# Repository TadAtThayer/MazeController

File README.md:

# MazeController
Arduino Shield for ES28 project

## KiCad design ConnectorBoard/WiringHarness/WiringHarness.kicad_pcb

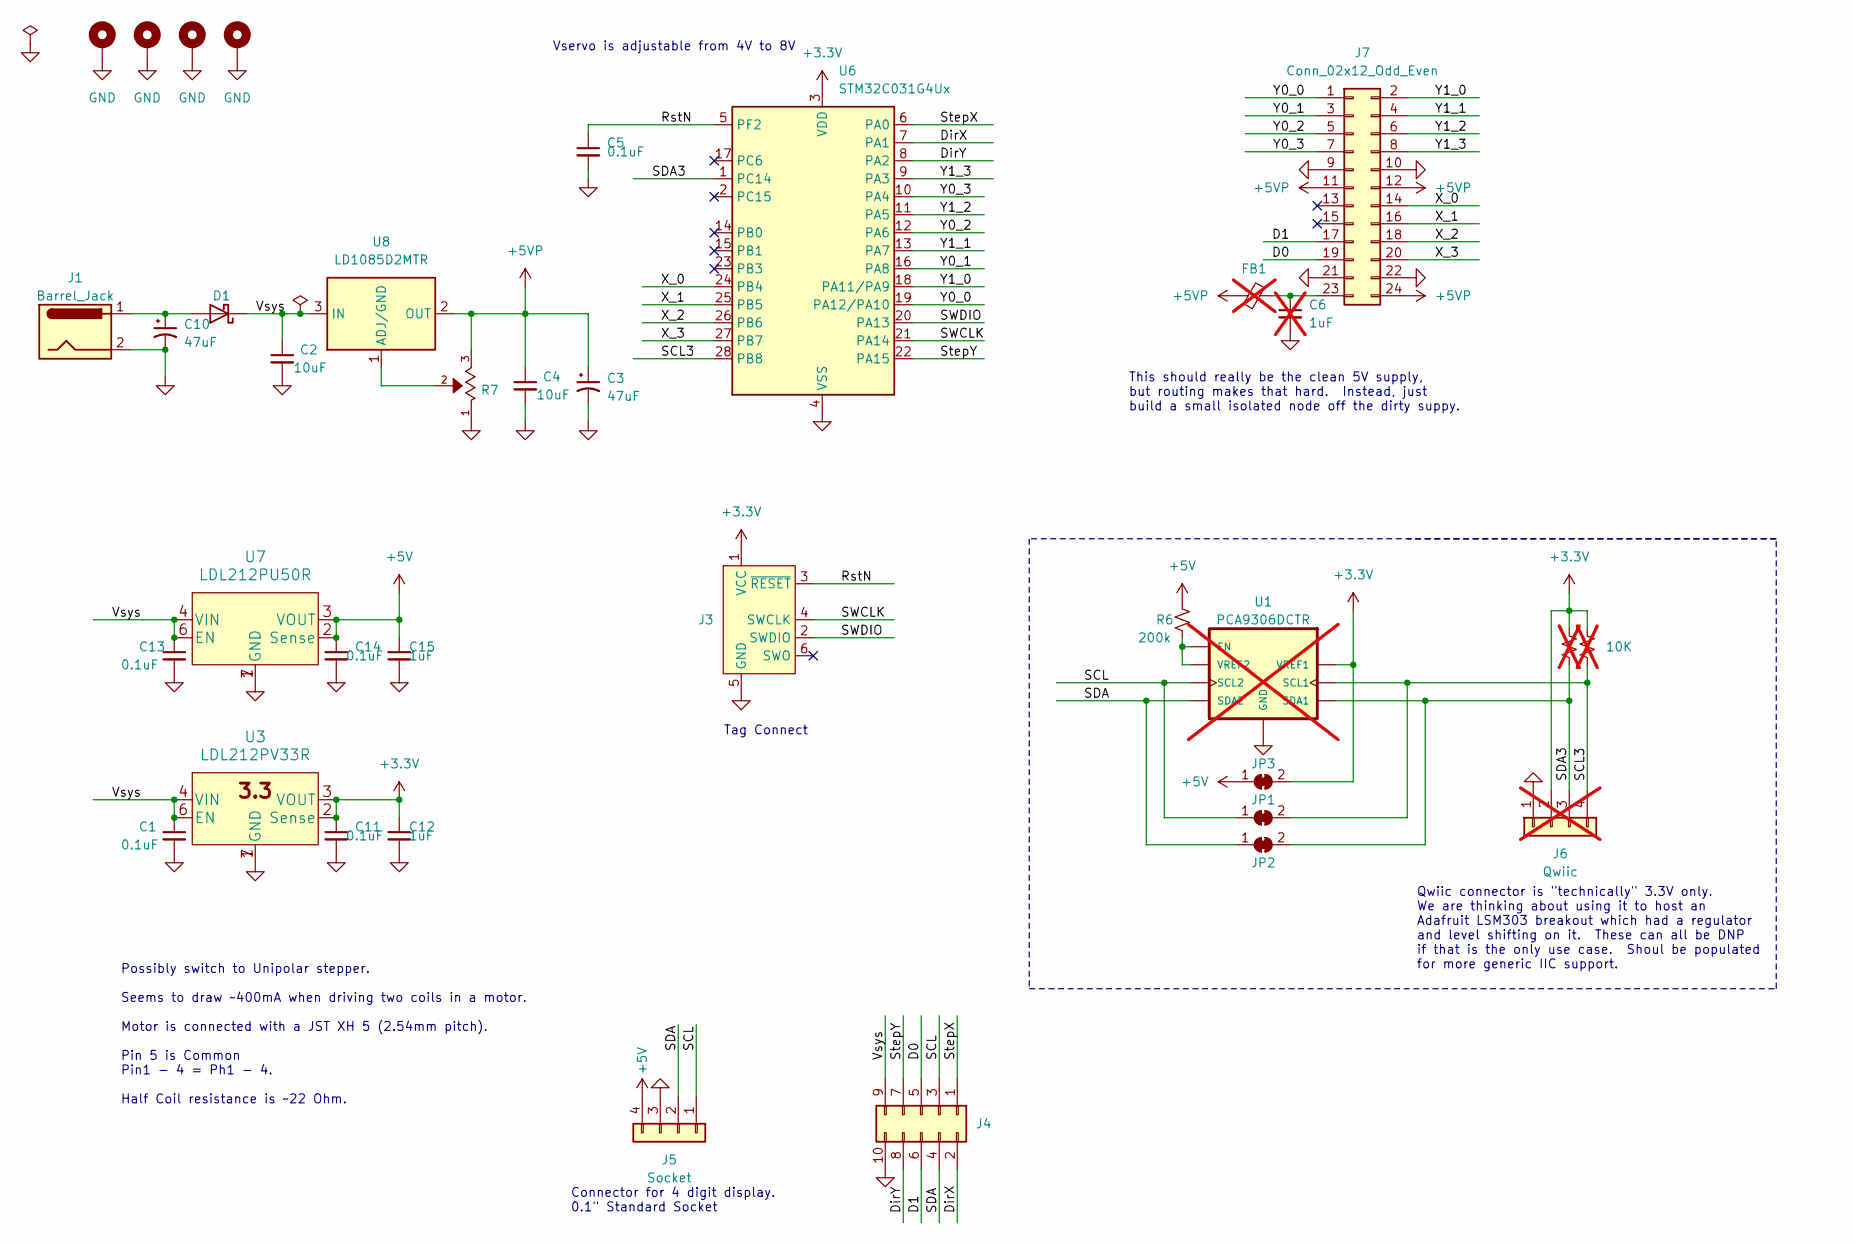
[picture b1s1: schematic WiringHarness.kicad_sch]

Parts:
C1, C5, C11, C13, C14: 0.1uF; C_0603_1608Metric; Digikey 1276-1861-1-ND
C2, C4: 10uF; C_0805_2012Metric; Digikey 490-10500-1-ND
C3, C10: 47uF; CP_Radial_D6.3mm_P2.50mm; Digikey 10-ECE-A1EKA470ICT-ND
C6: C_1U; C_0603_1608Metric; MPN CL10B105KA8NFNC; DigiKey PN 1276-1942-1-ND; not fitted
C12, C15: 1uF; C_0603_1608Metric; Digikey 1276-1861-1-ND
D1: D_Schottky; D_SMA; Digikey SK36A-LTPMSCT-ND
FB1: FB_120_100MHz; L_0603_1608Metric; DigiKey PN 490-16660-1-ND; not fitted
H1, H2, H3, H5: MountingHole_Pad; MountingHole_2.2mm_M2_Pad
J1: Barrel_Jack; BarrelJack_Horizontal; Digikey CP-002A-ND
J3: Conn_ARM_SWD_TagConnect_TC2030-NL; Tag-Connect_TC2030-IDC-NL_2x03_P1.27mm_Vertical
J4: Conn_02x05_Odd_Even; PinHeader_2x05_P2.54mm_Vertical; Digikey 732-2094-ND
J5: Socket; PinSocket_1x04_P2.54mm_Vertical; Digikey S7037-ND
J6: Qwiic; JST_SH_SM04B-SRSS-TB_1x04-1MP_P1.00mm_Horizontal; Digikey SM04B-SRSS-TB; not fitted
J7: Conn_02x12_Odd_Even; PinHeader_2x12_P2.54mm_Horizontal; Digikey 2057-PH2RA-24-UA-ND
JP1, JP2, JP3: SolderJumper_2_Bridged; SolderJumper-2_P1.3mm_Bridged_RoundedPad1.0x1.5mm
R1, R2: 10K; R_0603_1608Metric; Digikey RMCF0603FT10K0CT-ND; not fitted
R6: 200k; R_0603_1608Metric; Digikey RMCF0603FT200KCT-ND
R7: TC33X-2-102E; TRIM_TC33X-2-201E; Digikey TC33X-103ECT-ND
U1: PCA9306DCTR; MSOP-8_3x3mm_P0.65mm; Digikey 296-18509-1-ND; not fitted
U3: LDL212PV33R; LDL212_2x2mm_Pitch0.5mm; Digikey 497-19548-1-ND
U6: STM32C031G4Ux; QFN-28_4x4mm_P0.5mm; Digikey 497-STM32C031G6U6-ND
U7: LDL212PU50R; LDL212_3x3mm_Pitch0.95mm; Digikey 497-16897-1-ND
U8: LD1085D2MTR; TO-263-3_TabPin2; Digikey 497-3419-1-ND

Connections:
+3.3V: C11.1, C12.1, J3.1 (VCC), J6.2, JP3.2 (B), R1.1, R2.1, U1.2 (VREF1), U3.2 (Sense), U3.3 (VOUT), U6.3 (VDD)
+5V: C14.1, C15.1, J5.4, JP3.1 (A), R6.1, U7.2 (Sense), U7.3 (VOUT)
+5VP: C3.1, C4.1, FB1.1, J7.11, J7.12, J7.24, R7.3, U8.2 (OUT)
/D0: J4.5, J7.19
/D1: J4.6, J7.17
/DirX: J4.2, U6.7 (PA1)
/DirY: J4.8, U6.8 (PA2)
/RstN: C5.1, J3.3 (~RESET), U6.5 (PF2)
/SCL: J4.3, J5.1, JP1.1 (A), U1.6 (SCL2)
/SCL3: J6.4, JP1.2 (B), R1.2, U1.3 (SCL1), U6.28 (PB8)
/SDA: J4.4, J5.2, JP2.1 (A), U1.5 (SDA2)
/SDA3: J6.3, JP2.2 (B), R2.2, U1.4 (SDA1), U6.1 (PC14)
/SWCLK: J3.4 (SWCLK), U6.21 (PA14)
/SWDIO: J3.2 (SWDIO), U6.20 (PA13)
/StepX: J4.1, U6.6 (PA0)
/StepY: J4.7, U6.22 (PA15)
/Vsys: C1.1, C2.1, C13.1, D1.1 (K), J4.9, U3.4 (VIN), U3.6 (EN), U7.4 (VIN), U7.6 (EN), U8.3 (IN)
/X_0: J7.14, U6.24 (PB4)
/X_1: J7.16, U6.25 (PB5)
/X_2: J7.18, U6.26 (PB6)
/X_3: J7.20, U6.27 (PB7)
/Y0_0: J7.1, U6.19 (PA12/PA10)
/Y0_1: J7.3, U6.16 (PA8)
/Y0_2: J7.5, U6.12 (PA6)
/Y0_3: J7.7, U6.10 (PA4)
/Y1_0: J7.2, U6.18 (PA11/PA9)
/Y1_1: J7.4, U6.13 (PA7)
/Y1_2: J7.6, U6.11 (PA5)
/Y1_3: J7.8, U6.9 (PA3)
GND: C1.2, C2.2, C3.2, C4.2, C5.2, C6.2, C10.2, C11.2, C12.2, C13.2, C14.2, C15.2, H1.1, H2.1, H3.1, H5.1, J1.2, J3.5 (GND), J4.10, J5.3, J6.1, J7.9, J7.10, J7.21, J7.22, R7.1, U1.1 (GND), U3.1 (GND), U3.7 (GND), U6.4 (VSS), U7.1 (GND), U7.7 (GND)
unnamed: C10.1, D1.2 (A), J1.1
unnamed: C6.1, FB1.2, J7.23
unnamed: R6.2, U1.7 (VREF2), U1.8 (EN)
unnamed: R7.2, U8.1 (ADJ/GND)

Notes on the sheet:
This should really be the clean 5V supply, but routing makes that hard. Instead, just build a small isolated node off the dirty suppy.
Connector for 4 digit display. 0.1" Standard Socket
Vservo is adjustable from 4V to 8V
Possibly switch to Unipolar stepper. Seems to draw ~400mA when driving two coils in a motor. Motor is connected with a JST XH 5 (2.54mm pitch). Pin 5 is Common Pin1 - 4 = Ph1 - 4. Half Coil resistance is ~22 Ohm.
Qwiic connector is "technically" 3.3V only. We are thinking about using it to host an Adafruit LSM303 breakout which had a regulator and level shifting on it. These can all be DNP if that is the only use case. Shoul be populated for more generic IIC support.
Tag Connect

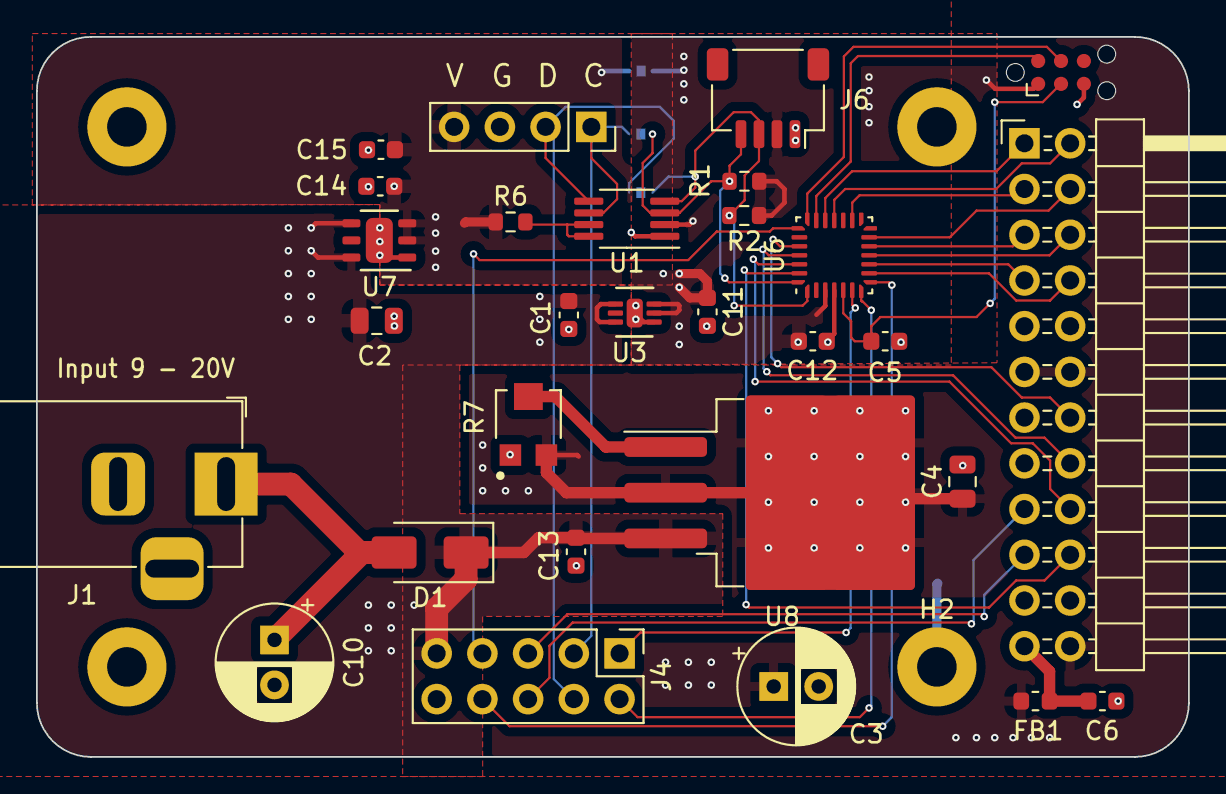
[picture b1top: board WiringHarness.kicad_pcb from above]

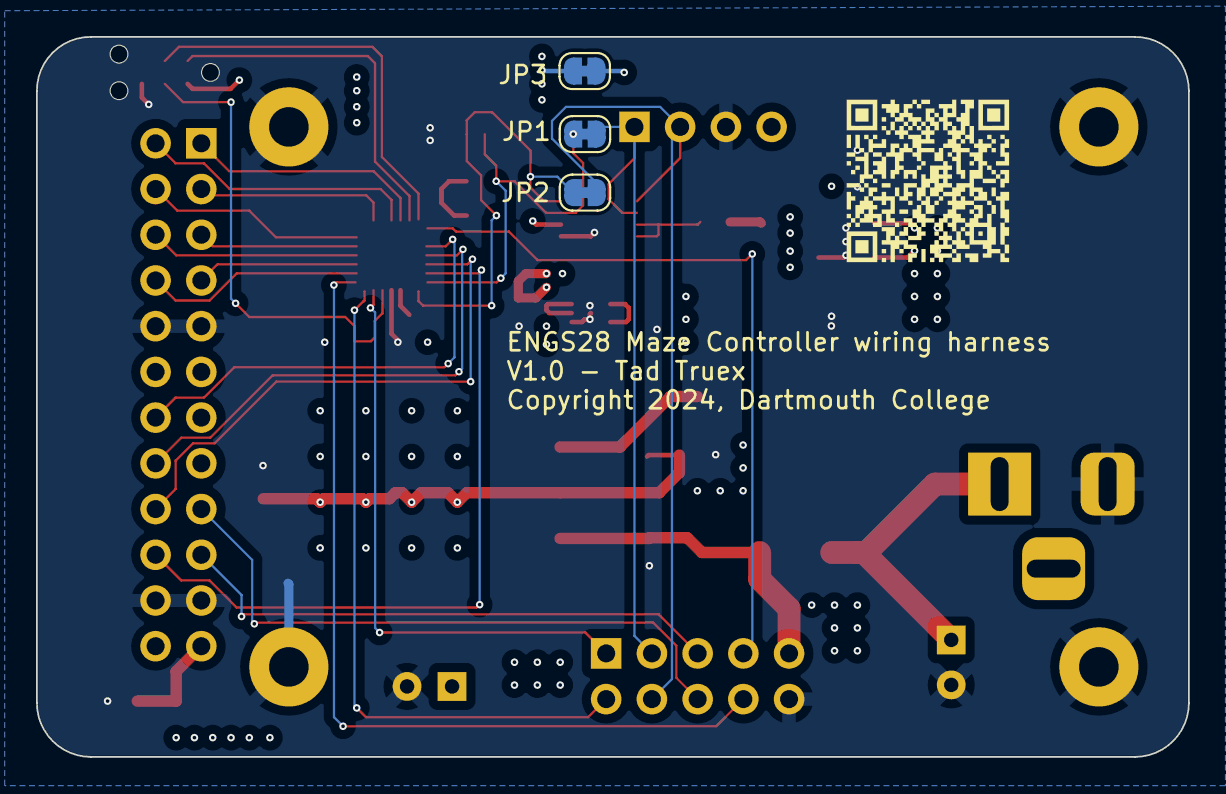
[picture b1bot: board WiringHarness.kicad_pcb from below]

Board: 4 copper layers, 64.0 x 40.0 mm, 36 parts (3 on the bottom side), 34 nets.

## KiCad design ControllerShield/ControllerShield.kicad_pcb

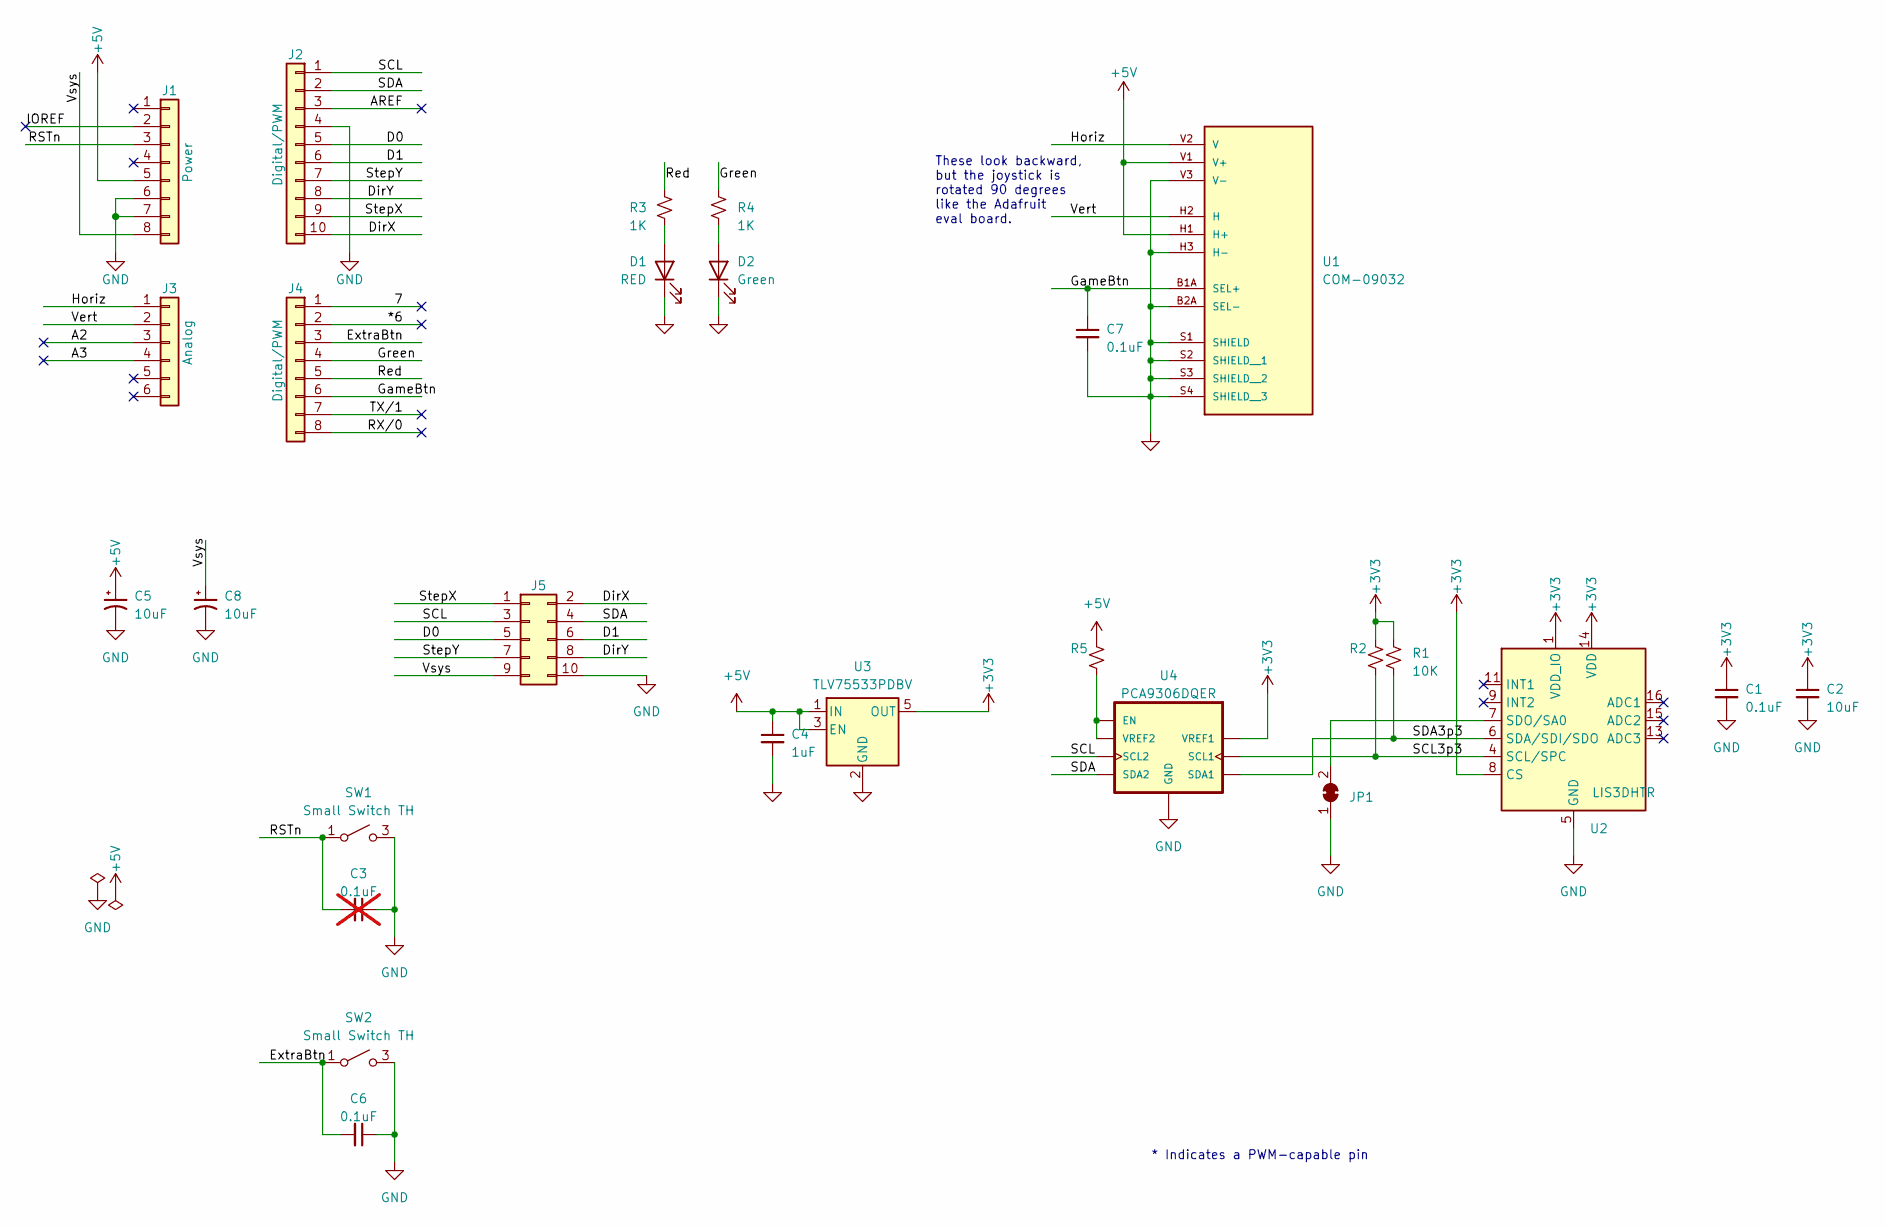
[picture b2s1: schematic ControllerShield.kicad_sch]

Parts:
C1, C6, C7: 0.1uF; C_0603_1608Metric; Digikey 1276-1000-1-ND
C2: 10uF; C_0603_1608Metric; Digikey 490-GRM188R61E106KA73JCT-ND
C3: 0.1uF; C_0603_1608Metric; Digikey 1276-1000-1-ND; not fitted
C4: 1uF; C_0603_1608Metric
C5, C8: 10uF; CP_Radial_D6.3mm_P2.50mm
D1: RED; LED_D5.0mm; Digikey 1125-1188-ND
D2: Green; LED_D5.0mm; Digikey 1125-1184-ND
J1: Power; PinSocket_1x08_P2.54mm_Vertical
J2: Digital/PWM; PinSocket_1x10_P2.54mm_Vertical
J3: Analog; PinSocket_1x06_P2.54mm_Vertical
J4: Digital/PWM; PinSocket_1x08_P2.54mm_Vertical
J5: Conn_02x05_Odd_Even; PinHeader_2x05_P2.54mm_Vertical; Digikey 732-2094-ND
JP1: SolderJumper_2_Bridged; SolderJumper-2_P1.3mm_Bridged_RoundedPad1.0x1.5mm
R1, R2: 10K; R_0603_1608Metric; Digikey RMCF0603FT10K0CT-ND
R3, R4: 1K; R_0603_1608Metric; Digikey RMCF0603FT1K00CT-ND
R5: 200K; R_0603_1608Metric; Digikey RMCF0603FT10K0CT-ND
SW1, SW2: Small Switch TH; SW4_1825910-B_TEC; Digikey 450-1650-ND
U1: COM-09032; XDCR_COM-09032
U2: LIS3DHTR; LGA-16_3x3mm_P0.5mm_LayoutBorder3x5y; Digikey 497-10613-1-ND
U3: TLV75533PDBV; SOT-23-5; Digikey 296-50411-1-ND
U4: PCA9306DQER; TSSOP-8_3x3mm_P0.65mm; DigiKey 296-18509-2-ND

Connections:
+3V3: C1.1, C2.1, R1.1, R2.1, U2.1 (VDD_IO), U2.8 (CS), U2.14 (VDD), U3.5 (OUT), U4.2 (VREF1)
+5V: C4.1, C5.1, J1.5, R5.1, U1.H1 (H+), U1.V1 (V+), U3.1 (IN), U3.3 (EN)
/7: J4.1
/*6: J4.2
/A2: J3.3
/A3: J3.4
/AREF: J2.3
/D0: J2.5, J5.5
/D1: J2.6, J5.6
/DirX: J2.10, J5.2
/DirY: J2.8, J5.8
/ExtraBtn: C6.2, J4.3, SW2.1 (A), SW2.2 (A)
/GameBtn: C7.1, J4.6, U1.B1A (SEL+)
/Green: J4.4, R4.1
/Horiz: J3.1, U1.V2 (V)
/IOREF: J1.2
/RSTn: C3.2, J1.3, SW1.1 (A), SW1.2 (A)
/RX/0: J4.8
/Red: J4.5, R3.1
/SCL: J2.1, J5.3, U4.6 (SCL2)
/SCL3p3: R2.2, U2.4 (SCL/SPC), U4.3 (SCL1)
/SDA: J2.2, J5.4, U4.5 (SDA2)
/SDA3p3: R1.2, U2.6 (SDA/SDI/SDO), U4.4 (SDA1)
/StepX: J2.9, J5.1
/StepY: J2.7, J5.7
/TX/1: J4.7
/Vert: J3.2, U1.H2 (H)
/Vsys: C8.1, J1.8, J5.9
GND: C1.2, C2.2, C3.1, C4.2, C5.2, C6.1, C7.2, C8.2, D1.1 (K), D2.1 (K), J1.6, J1.7, J2.4, J5.10, JP1.1 (A), SW1.3 (B), SW1.4 (B), SW2.3 (B), SW2.4 (B), U1.B2A (SEL-), U1.H3 (H-), U1.S1 (SHIELD), U1.S2 (SHIELD__1), U1.S3 (SHIELD__2), U1.S4 (SHIELD__3), U1.V3 (V-), U2.5 (GND), U2.10 (GND), U2.12 (GND), U3.2 (GND), U4.1 (GND)
unnamed: D1.2 (A), R3.2
unnamed: D2.2 (A), R4.2
unnamed: JP1.2 (B), U2.7 (SDO/SA0)
unnamed: R5.2, U4.7 (VREF2), U4.8 (EN)

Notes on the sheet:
These look backward, but the joystick is rotated 90 degrees like the Adafruit eval board.
* Indicates a PWM-capable pin

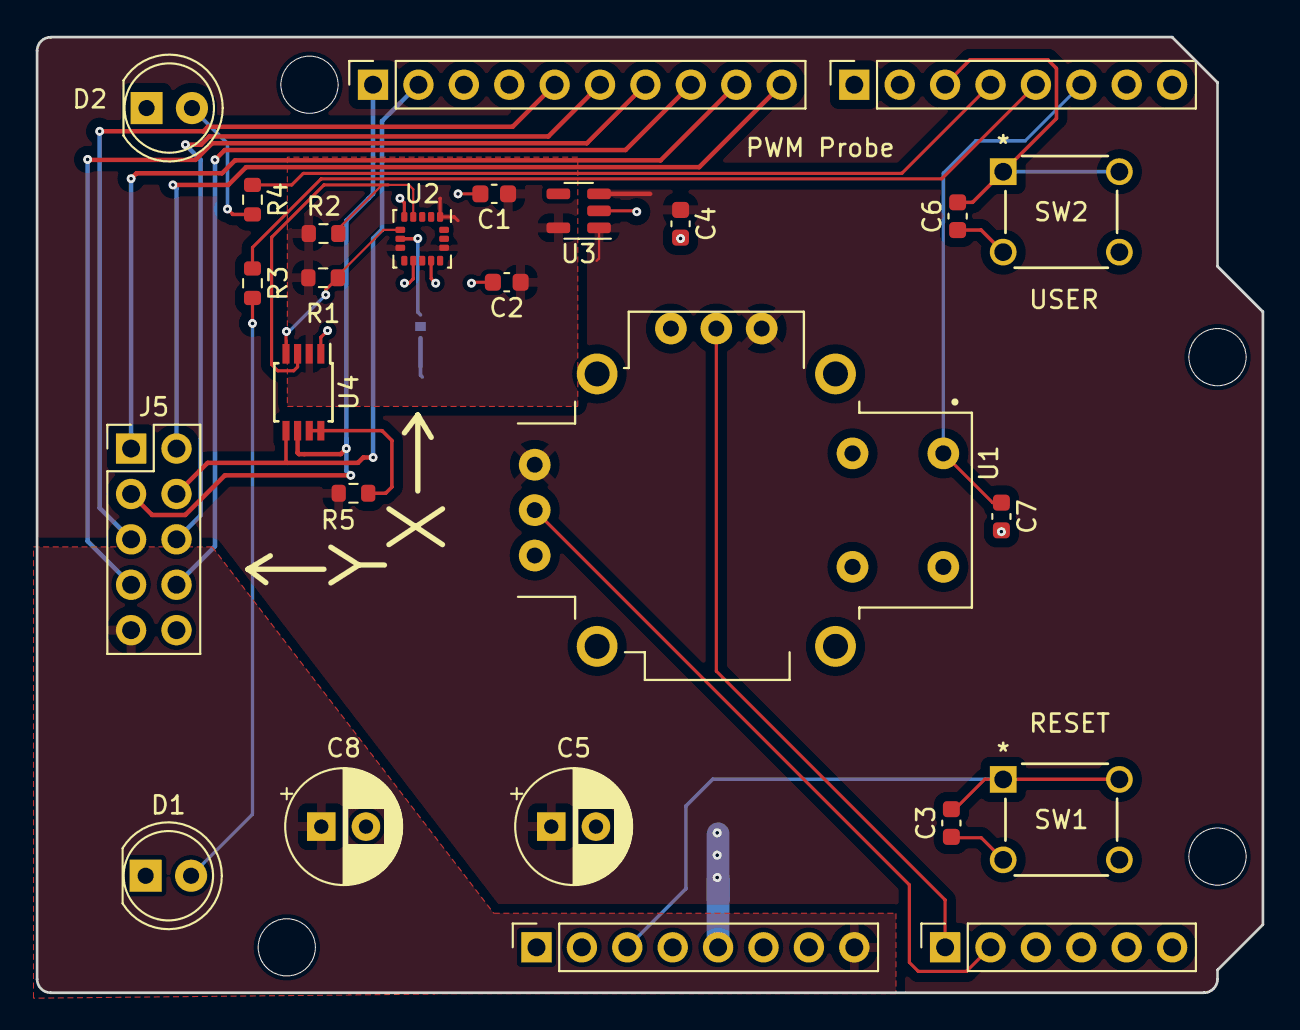
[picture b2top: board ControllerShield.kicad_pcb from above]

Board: 2 copper layers, 68.6 x 53.5 mm, 31 parts (1 on the bottom side), 25 nets.

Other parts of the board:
MH1, MH2, MH3, MH4: MountingHole_3.2mm

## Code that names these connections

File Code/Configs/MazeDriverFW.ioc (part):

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Mcu.Name=STM32C031G(4-6)Ux
Mcu.Package=UFQFPN28
Mcu.UserName=STM32C031G4Ux
PA0.GPIOParameters=GPIO_Label
PA0.GPIO_Label=StepX
PA0.Signal=GPIO_Input
PA1.GPIOParameters=GPIO_Label
PA1.GPIO_Label=DirX
PA1.Signal=GPIO_Input
PA11\ [PA9].GPIOParameters=GPIO_Label
PA11\ [PA9].GPIO_Label=Y1_0
PA11\ [PA9].Signal=GPIO_Input
PA12\ [PA10].GPIOParameters=GPIO_Label
PA12\ [PA10].GPIO_Label=Y0_0
PA12\ [PA10].Signal=GPIO_Input
PA13.GPIOParameters=GPIO_Label
PA13.GPIO_Label=SWDIO
PA13.Mode=Serial_Wire
PA13.Signal=DEBUG_SWDIO
PA14-BOOT0.GPIOParameters=GPIO_Label
PA14-BOOT0.GPIO_Label=SWCLK
PA14-BOOT0.Mode=Serial_Wire
PA14-BOOT0.Signal=DEBUG_SWCLK
PA15.GPIOParameters=GPIO_Label
PA15.GPIO_Label=StepY
PA15.Signal=GPXTI15
PA2.GPIOParameters=GPIO_Label
PA2.GPIO_Label=DirY
PA2.Signal=GPIO_Input
PA3.GPIOParameters=GPIO_Label
PA3.GPIO_Label=Y1_3
PA3.Signal=GPIO_Output
PA4.GPIOParameters=GPIO_Label
PA4.GPIO_Label=Y0_3
PA4.Signal=GPIO_Output
PA5.GPIOParameters=GPIO_Label
PA5.GPIO_Label=Y1_2
PA5.Signal=GPIO_Output
PA6.GPIOParameters=GPIO_Label
PA6.GPIO_Label=Y0_2
PA6.Signal=GPIO_Output
PA7.GPIOParameters=GPIO_Label
PA7.GPIO_Label=Y1_1
PA7.Signal=GPIO_Output
PA8.GPIOParameters=GPIO_Label
PA8.GPIO_Label=Y0_1
PA8.Signal=GPXTI8
PB4.GPIOParameters=GPIO_Label
PB4.GPIO_Label=X_0
PB4.Signal=GPIO_Output
PB5.GPIOParameters=GPIO_Label
PB5.GPIO_Label=X_1
PB5.Signal=GPIO_Output
PB6.GPIOParameters=GPIO_Label
PB6.GPIO_Label=X_2
PB6.Signal=GPIO_Output
PB7.GPIOParameters=GPIO_Label
PB7.GPIO_Label=X_3
PB7.Signal=GPIO_Output
PB8.GPIOParameters=GPIO_Label
PB8.GPIO_Label=SCL3
PB8.Mode=I2C
PB8.Signal=I2C1_SCL
PC14-OSCX_IN\ (PC14).GPIOParameters=GPIO_Label
PC14-OSCX_IN\ (PC14).GPIO_Label=SDA3
PC14-OSCX_IN\ (PC14).Mode=I2C
PC14-OSCX_IN\ (PC14).Signal=I2C1_SDA
PF2-NRST.GPIOParameters=GPIO_Label
PF2-NRST.GPIO_Label=RstN
PF2-NRST.Signal=GPIO_Input
RCC.HSE_VALUE=8000000
RCC.SYSCLKFreq_VALUE=12000000
board=custom

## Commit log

2023-10-06 start wiring harness
2023-10-09 Wiring harness probably OK
2023-10-10 Add right angle ribbon cable to wiring harness
2023-10-10 Rounded corners and version string
2023-10-10 Add QR code
2023-10-11 start controller
2023-10-11 Tweak the connector board a bit. Rearrange X and Y. May do more depending on the other board.
2023-10-21 updates to connector
2023-10-23 decent candidate for rev 0.5wh
2023-10-23 Like 0.5 candidate
2023-10-23 fix step file
2023-10-24 attempt to make the library directory relative.
2023-10-24 add pullups for 3.3 version of I2C bus.
2023-10-24 Not sure what changes, but it was minor...
2023-10-26 work on controller
2023-10-27 variable servo source
2023-10-30 Possible release candidate for Controller Board.
2023-10-31 Add switch to controller
2023-10-31 add probe points
2023-10-31 generate gerbers
2023-10-31 Release candidate for controller board
2023-11-01 need to remove these eventually
2023-11-16 initial rework and controller bom
2023-11-20 Fix the bias network on the regulator.
    Close #6
2023-11-20 Work on #10.
    Need to decide if the leadless package is easier to deal with than a small BGA.
    Not obvious it is.
2023-11-21 signal caps at servo connectors
2023-11-21 Add QR code in preparation for next release
    Add Cap to
    5V
    Buttons
    Add level shifter.
    Close #7
    Close #9
2023-11-21 Change footprint for level shifter to something more reasonable.
    Add lots of cap to controller.
    Add level shifter to controller
2023-11-21 Close #13
2023-11-21 update qr code and legend
2023-11-21 Add a second switch to the controller board.
    Generate V0.9 gerbers with QRCode.
2023-11-21 add zip file as sent to fab
2023-11-28 Hard to believe, but I had the resistors backward again on the regulator...
2023-11-29 add vendor id for level shifter
2024-01-04 add some docs
    Convert to STM32C031 based stepper version.
2024-01-04 fully connected and drc clean. Need to examine copper pours
2024-01-04 cleanup the pours a bit
2024-01-05 Update controller shield to match the new driver.
2024-01-05 Gerbers for both board V1.0
2024-01-05 fix vias
2024-01-07 Add some ide configs
2024-01-08 update names on dev board code
2024-01-16 probably a mistake
2024-01-16 work on firmware
2024-01-16 match names to schematic
2024-01-16 Fix #19 - no artwork changes
2024-01-16 work on step-dir
2024-01-16 add i2c address
2024-01-16 Start working on motion planner
2024-01-16 still pooping along
2024-01-16 cleanup queue a bit
2024-01-16 start fw devel
2024-01-16 turn on interrupts
2024-01-16 Code wip
2024-01-18 clock stretching seems to kill i2c with arduino
2024-01-19 initial stepper fw on board
2024-01-19 switch to step models for many components
2024-01-19 bom changes
2024-01-22 Switch move queu to contain a number of steps. This costs a bit in the interupt handler, but we're not running that fast, so we should be OK.
    This makes the queues much smaller.
2024-01-22 some test code to make sure (via logic analyzer) that the assemnly went ok
2024-01-23 WIP (not currently working)
    Motor test process. Must be done with the motors uncaged.
    Switch to a peek mode on the queues to make it easier for the planner to tell
    if there is any pending motion.
2024-01-23 wip no compile
2024-01-23 work on motor queue
2024-01-23 Motor Queue
2024-01-23 remove some optimization to help w/ debug
2024-01-24 cleanup and bug hunt
2024-01-25 working on step dir
2024-01-25 remove some dead code
2024-01-29 cleanup
2024-01-29 Work on y and yP mismatch
2024-01-30 Switch to half steps.
    Make the off time a register.
    Seems to fix the Y Y' offset issues.
2024-01-30 rename x and y inputs to account for maze rotation
2024-01-31 add a DNP to the schematic. Step/Dir works OK
2024-02-06 This is a bit of a CF.
    Working on self test for the driver board and noticed none of my new
    builds had functioning I2C. Flash an older working one with this code
    and it croaked.
    Going to do some git spelunking to find out why or at least when.
2024-02-06 Found it
2024-02-07 add host address to 7 seg as i2c test
2024-02-08 Major cleanup/re-org. Working on driver for display backpack.
    Noticed that we can't access the backpack when the host (joystick) is attached.
    Worth pursuing...
2024-02-09 add Pass to the bist
2024-02-12 make calibrate a bit quicker
2024-02-13 working on auto rev
2024-02-14 signs of i2c life
2024-02-15 less broken
2024-02-20 Decent functionality
2024-02-21 Update test program to work with motors installed
2025-04-23 No idea what has changed here. Probably need to diff this again main...

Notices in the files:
ConnectorBoard/WiringHarness/WiringHarness.kicad_pcb:
Copyright 2024, Dartmouth College
